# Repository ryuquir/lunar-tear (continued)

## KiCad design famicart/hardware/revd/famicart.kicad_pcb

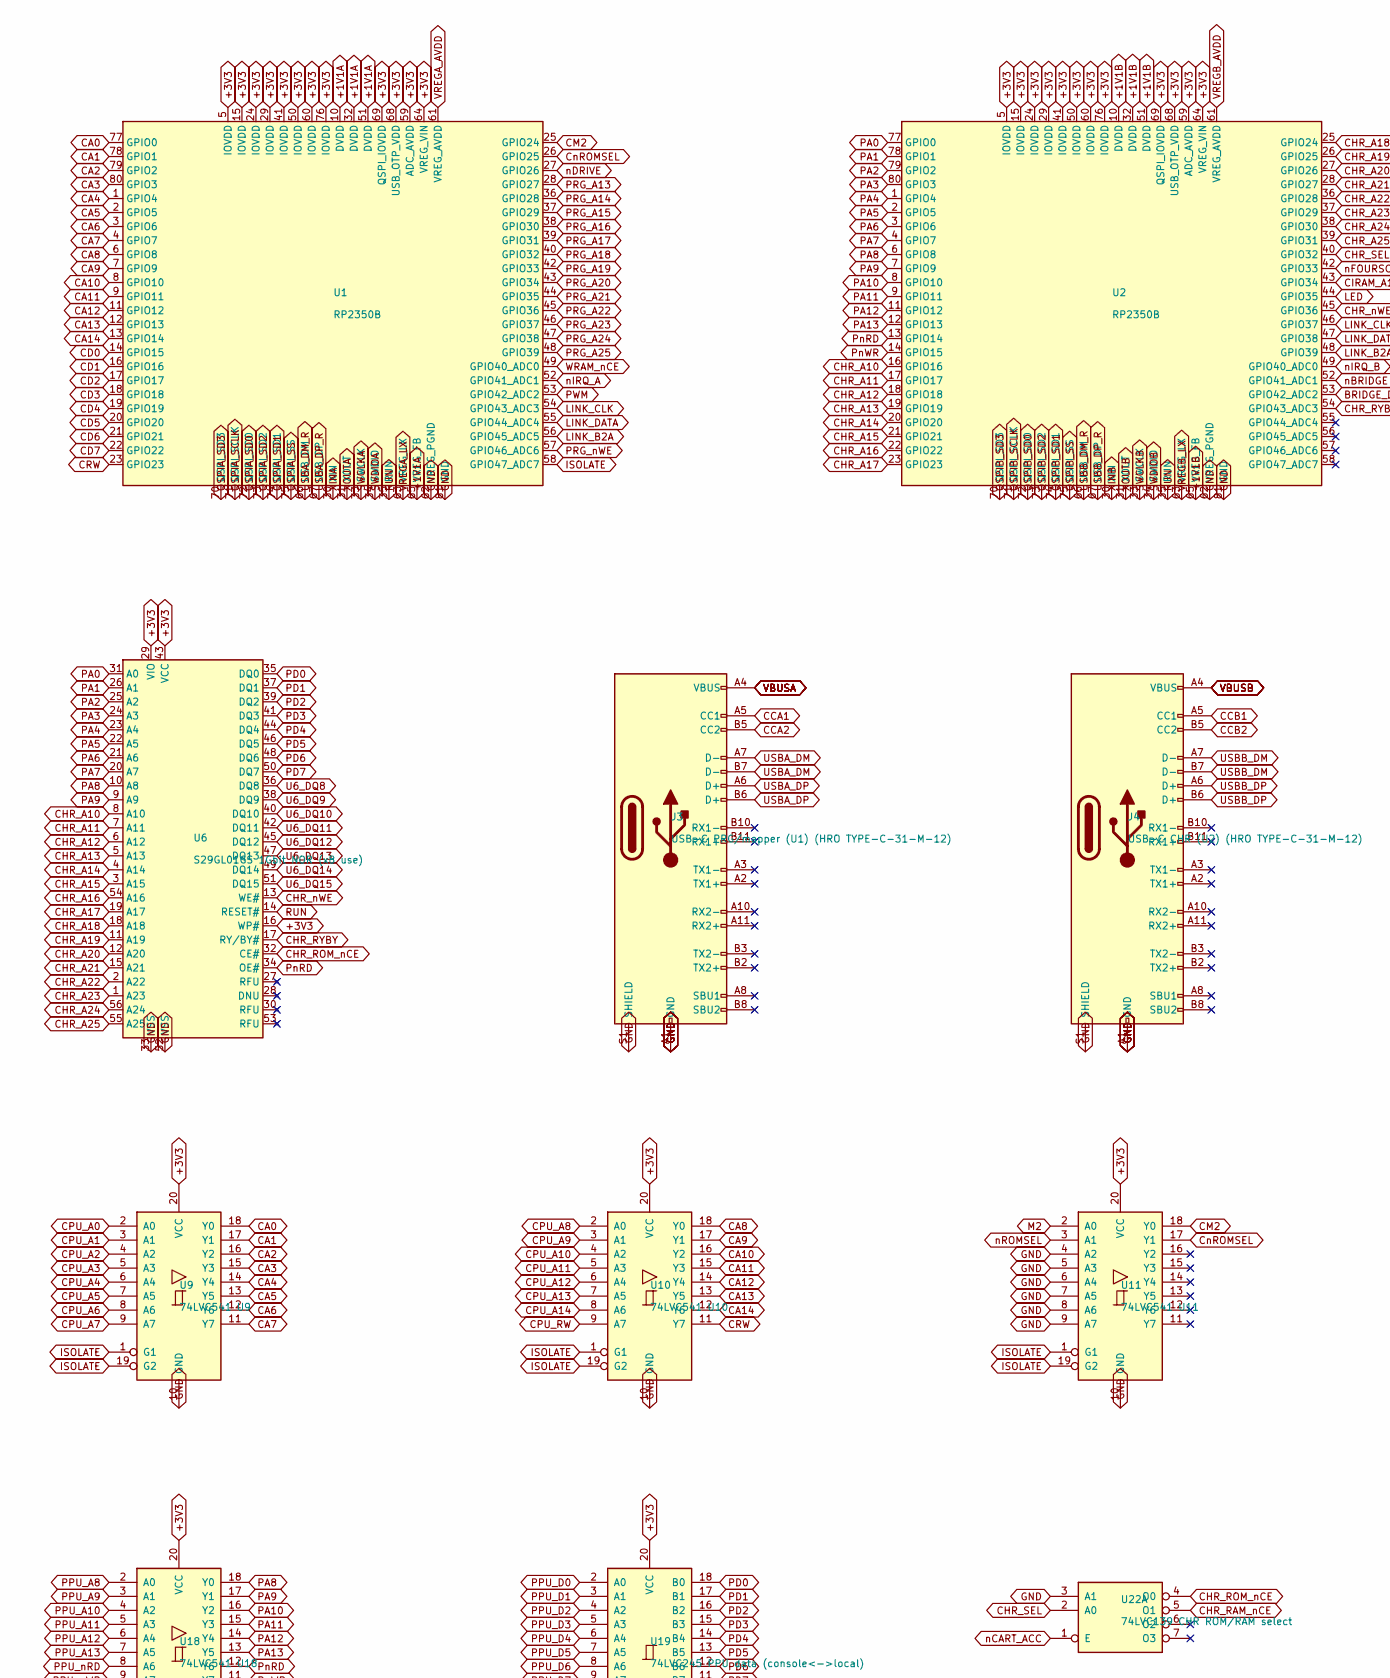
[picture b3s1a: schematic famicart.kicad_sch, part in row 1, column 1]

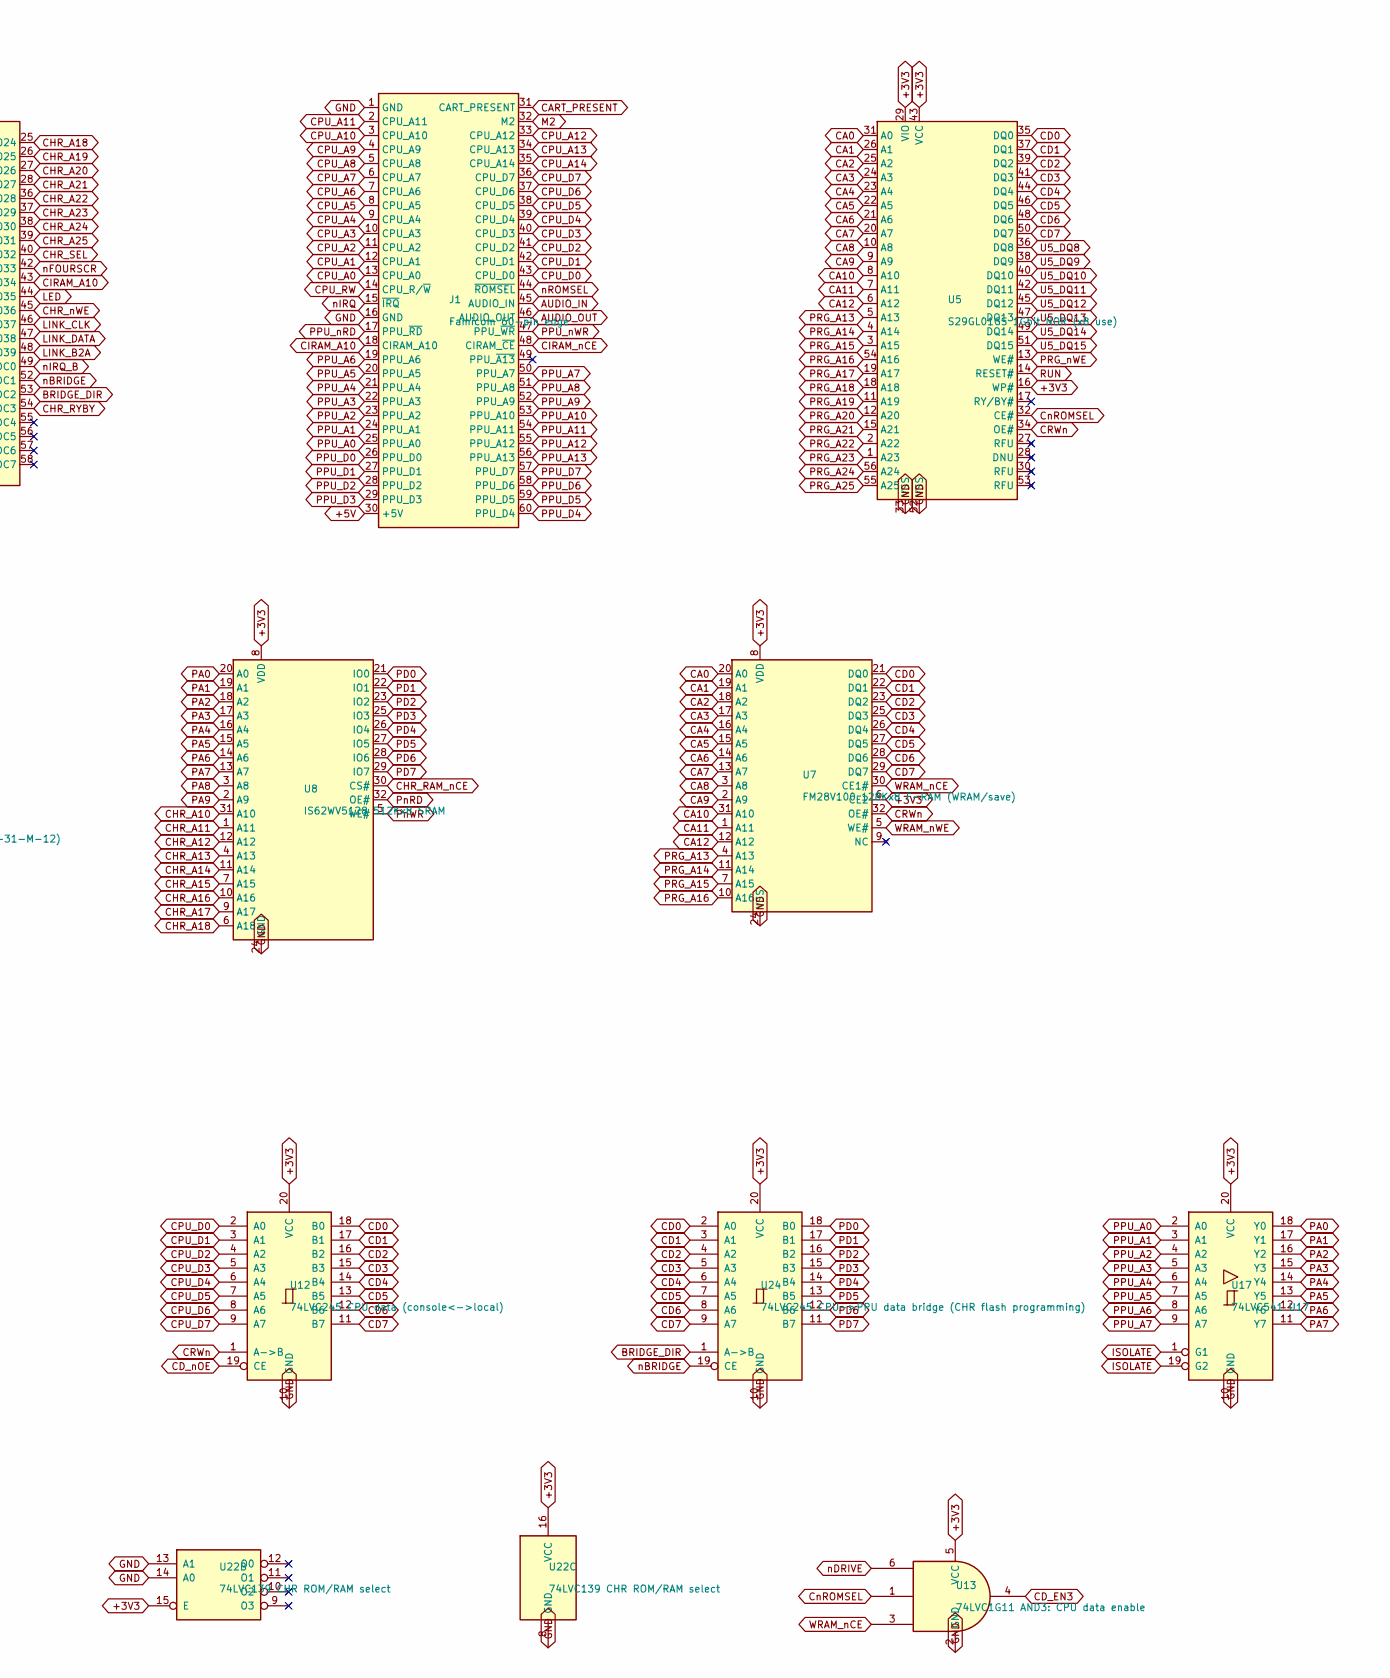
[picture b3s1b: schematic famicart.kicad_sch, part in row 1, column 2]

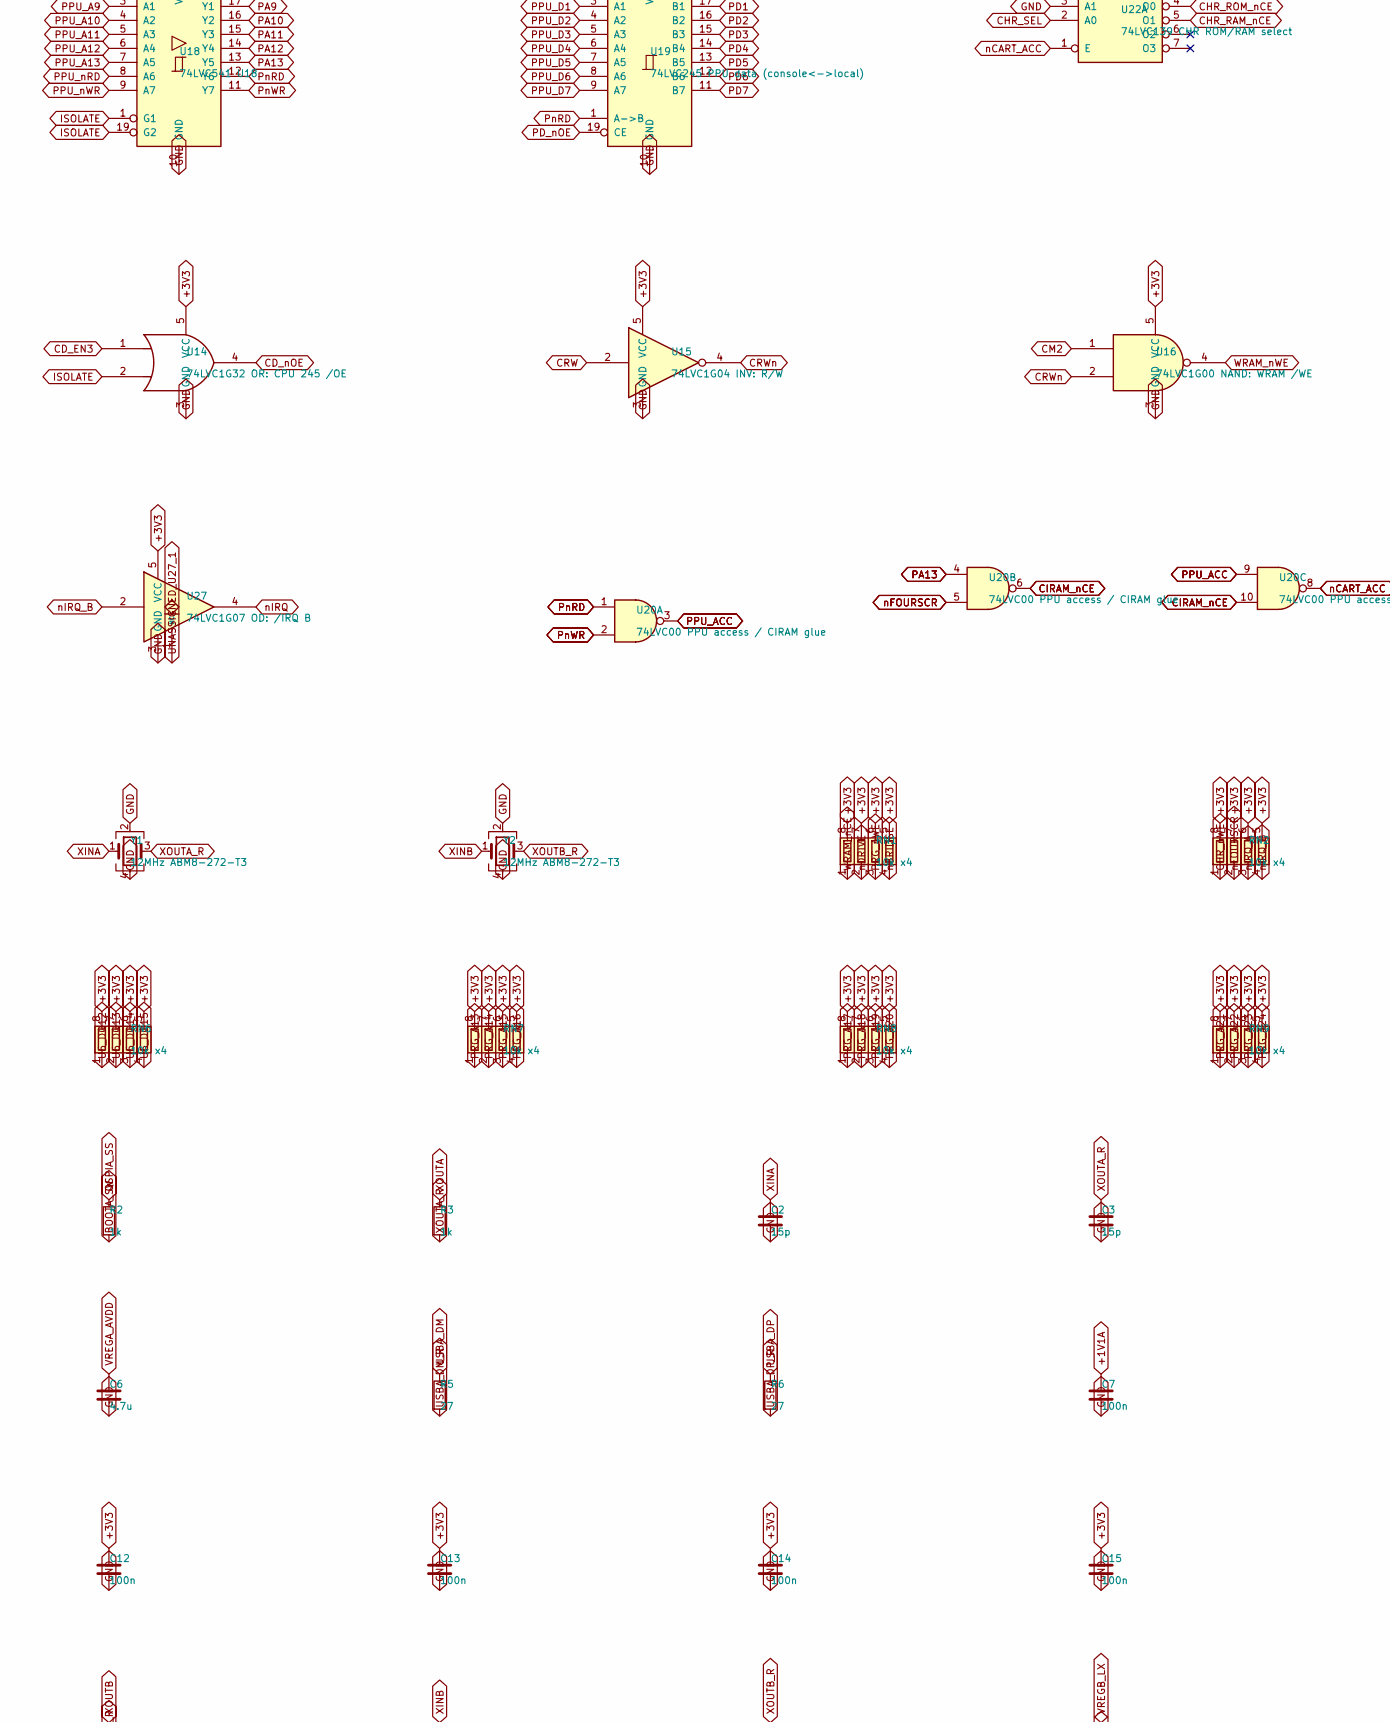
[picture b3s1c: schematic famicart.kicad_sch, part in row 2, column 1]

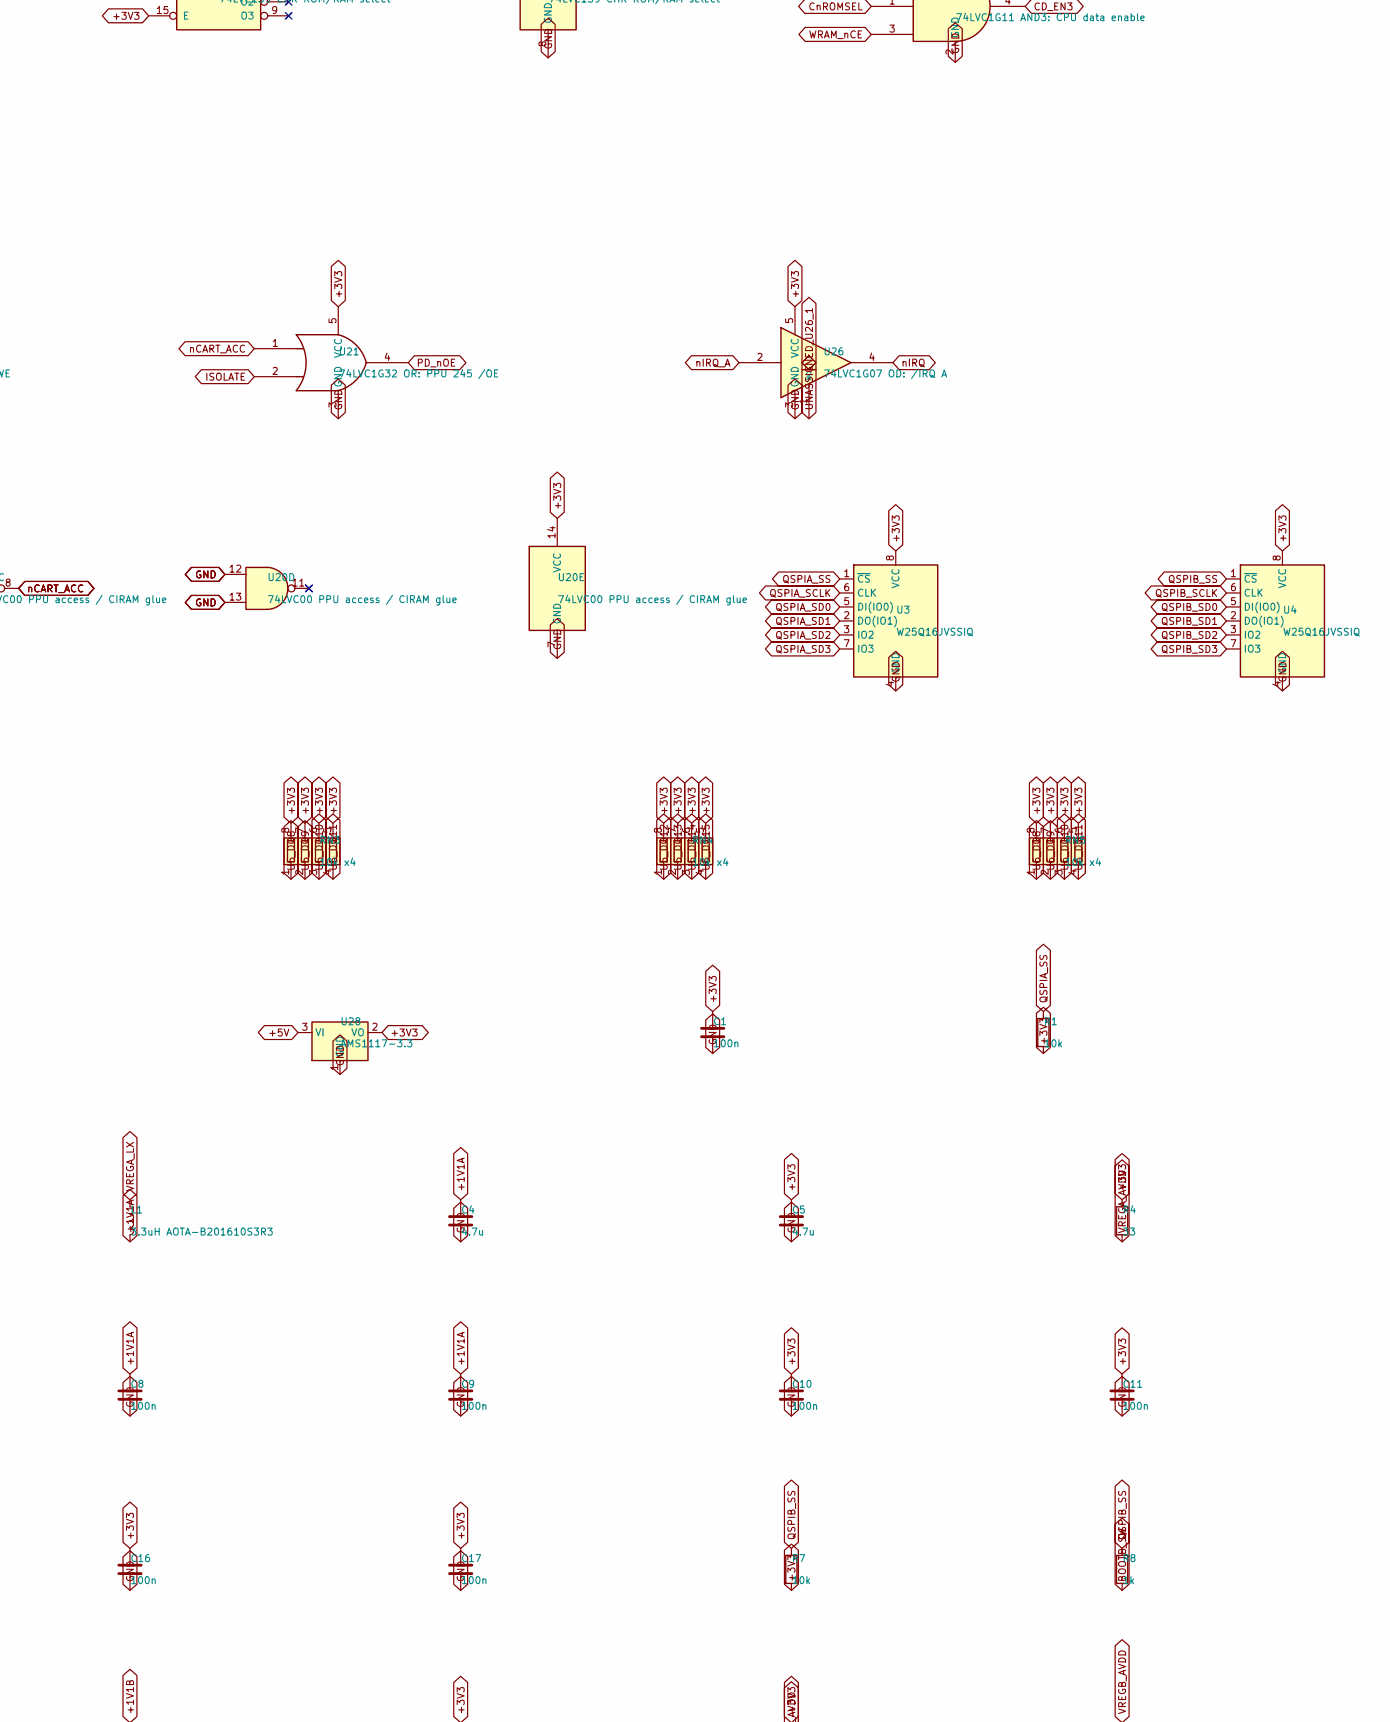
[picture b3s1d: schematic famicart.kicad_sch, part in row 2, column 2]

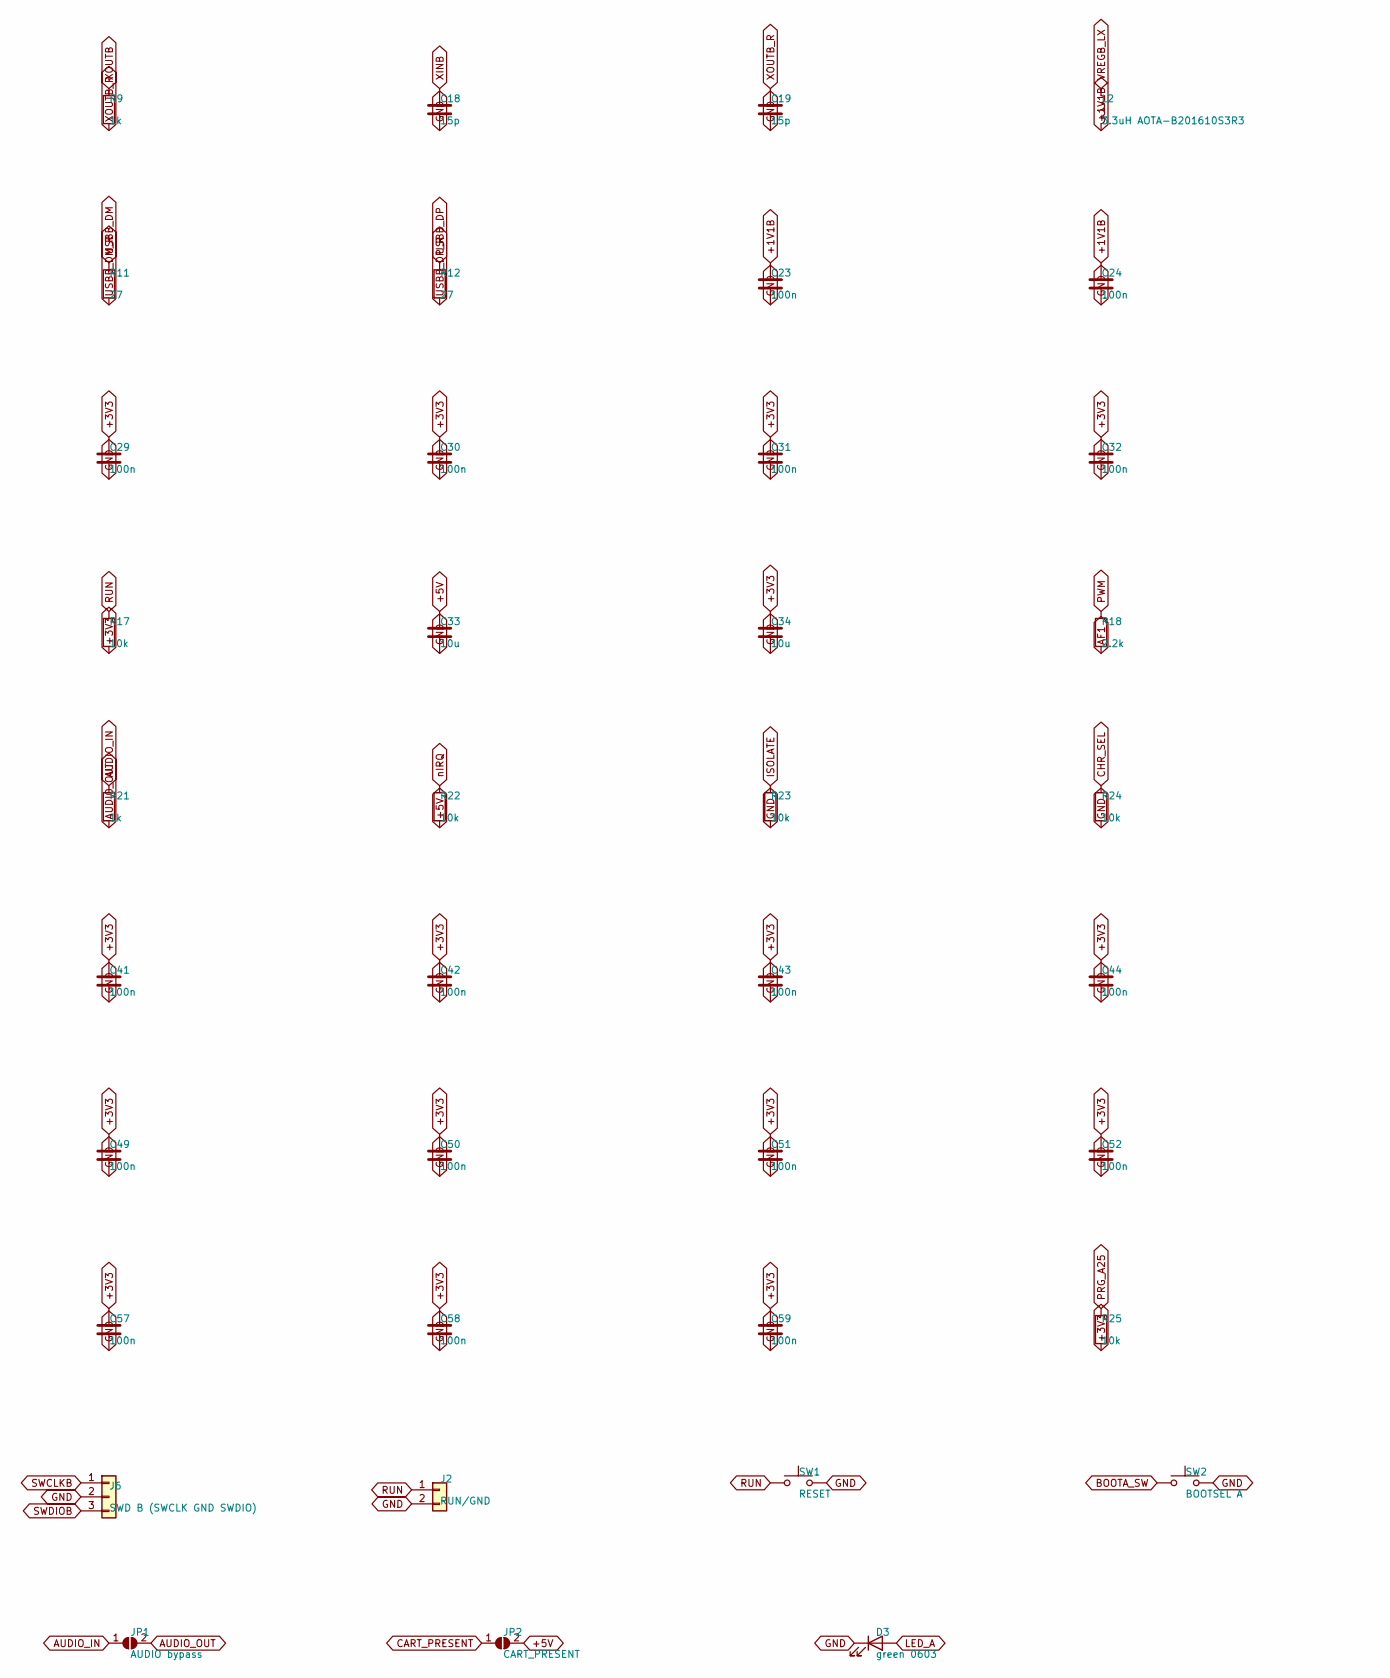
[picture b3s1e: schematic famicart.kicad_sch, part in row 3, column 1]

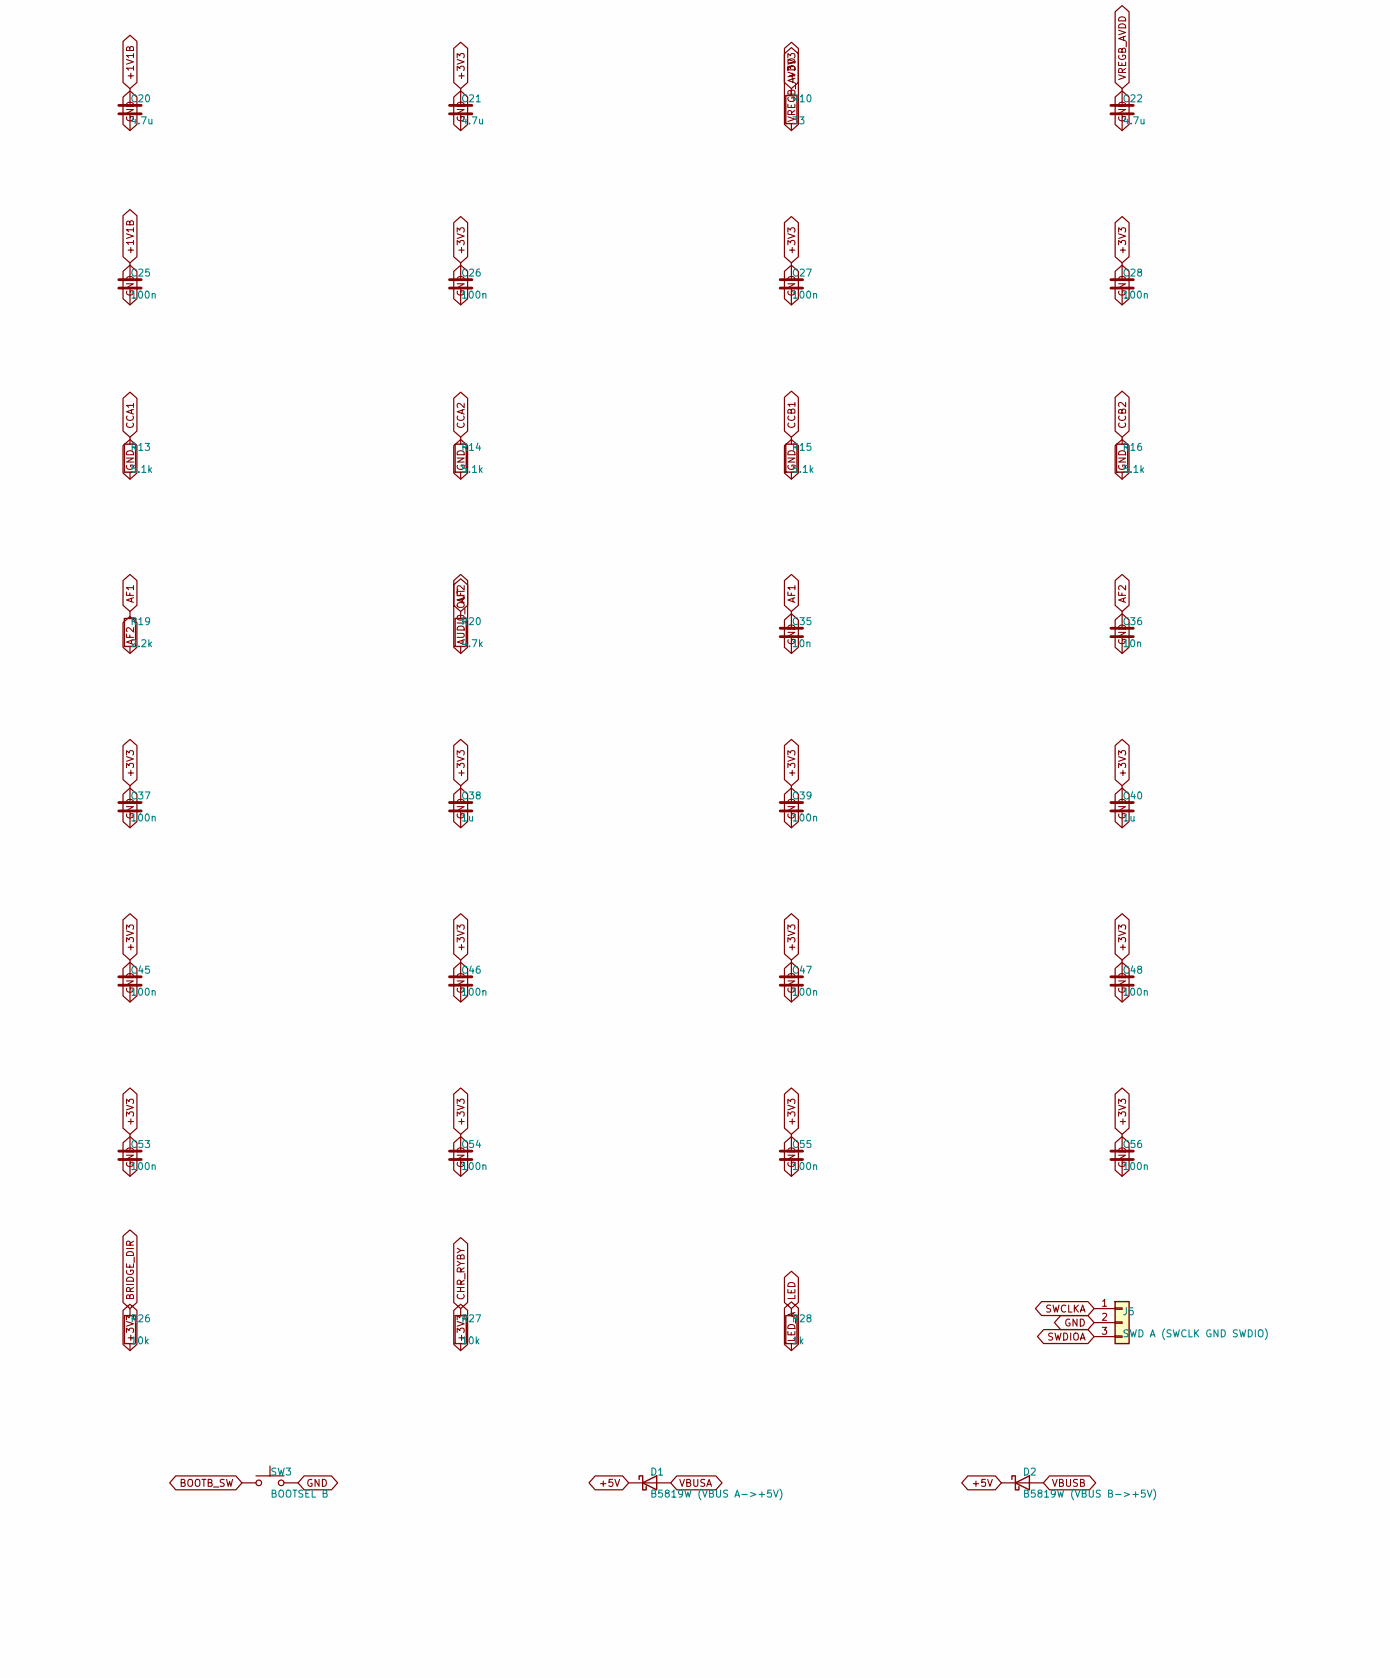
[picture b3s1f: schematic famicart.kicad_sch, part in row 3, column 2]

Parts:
C1, C17: 100n; C_0603_1608Metric
C2, C3, C18, C19: 15p; C_0402_1005Metric
C4, C5, C6, C20, C21, C22: 4.7u; C_0603_1608Metric
C7, C8, C9, C10, C11, C12, C13, C14, C15, C16, C23, C24, C25, C26, C27, C28, C29, C30, C31, C32, C37, C39, C41, C42, C43, C44, C45, C46, C47, C48, C49, C50, C51, C52, C53, C54, C55, C56, C57, C58, C59: 100n; C_0402_1005Metric
C33, C34: 10u; C_0805_2012Metric
C35, C36: 10n; C_0603_1608Metric
C38, C40: 1u; C_0603_1608Metric
D1: B5819W (VBUS A->+5V); D_SOD-123
D2: B5819W (VBUS B->+5V); D_SOD-123
D3: green 0603; LED_0603_1608Metric
J1: Famicom 60-pin edge; Famicom_CardEdge_60
J2: RUN/GND; PinHeader_1x02_P2.54mm_Vertical
J3: USB-C PRG/mapper (U1) (HRO TYPE-C-31-M-12); USB_C_Receptacle_HRO_TYPE-C-31-M-12
J4: USB-C CHR (U2) (HRO TYPE-C-31-M-12); USB_C_Receptacle_HRO_TYPE-C-31-M-12
J5: SWD A (SWCLK GND SWDIO); PinHeader_1x03_P2.54mm_Vertical
J6: SWD B (SWCLK GND SWDIO); PinHeader_1x03_P2.54mm_Vertical
JP1: AUDIO bypass; SolderJumper-2_P1.3mm_Open_RoundedPad1.0x1.5mm
JP2: CART_PRESENT; SolderJumper-2_P1.3mm_Open_RoundedPad1.0x1.5mm
L1, L2: 3.3uH AOTA-B201610S3R3; L_0806_2016Metric
R1, R7, R17, R22, R23, R24, R25, R26, R27: 10k; R_0603_1608Metric
R2, R8, R21, R28: 1k; R_0603_1608Metric
R3, R9: 1k; R_0402_1005Metric
R4, R10: 33; R_0402_1005Metric
R5, R6, R11, R12: 27; R_0603_1608Metric
R13, R14, R15, R16: 5.1k; R_0603_1608Metric
R18, R19: 2.2k; R_0603_1608Metric
R20: 4.7k; R_0603_1608Metric
RN1, RN2, RN3, RN4, RN5, RN6, RN7, RN8, RN9: 10k x4; R_Array_Convex_4x0603
SW1: RESET; SW_SPST_TL3342
SW2: BOOTSEL A; SW_SPST_TL3342
SW3: BOOTSEL B; SW_SPST_TL3342
U1, U2: RP2350B; QFN-80-1EP_10x10mm_P0.4mm_EP3.4x3.4mm
U3, U4: W25Q16JVSSIQ; SOIC-8_5.23x5.23mm_P1.27mm
U5, U6: S29GL01GS 1Gbit NOR (x8 use); TSOP-I-56_18.4x14mm_P0.5mm
U7: FM28V100 128Kx8 F-RAM (WRAM/save); TSOP-I-32_11.8x8mm_P0.5mm
U8: IS62WV5128 512Kx8 SRAM; TSOP-I-32_11.8x8mm_P0.5mm
U9: 74LVC541 U9; TSSOP-20_4.4x6.5mm_P0.65mm
U10: 74LVC541 U10; TSSOP-20_4.4x6.5mm_P0.65mm
U11: 74LVC541 U11; TSSOP-20_4.4x6.5mm_P0.65mm
U12: 74LVC245 CPU data (console<->local); TSSOP-20_4.4x6.5mm_P0.65mm
U13: 74LVC1G11 AND3: CPU data enable; SOT-23-6
U14: 74LVC1G32 OR: CPU 245 /OE; SOT-23-5
U15: 74LVC1G04 INV: R/W; SOT-23-5
U16: 74LVC1G00 NAND: WRAM /WE; SOT-23-5
U17: 74LVC541 U17; TSSOP-20_4.4x6.5mm_P0.65mm
U18: 74LVC541 U18; TSSOP-20_4.4x6.5mm_P0.65mm
U19: 74LVC245 PPU data (console<->local); TSSOP-20_4.4x6.5mm_P0.65mm
U20: 74LVC00 PPU access / CIRAM glue; TSSOP-14_4.4x5mm_P0.65mm
U21: 74LVC1G32 OR: PPU 245 /OE; SOT-23-5
U22: 74LVC139 CHR ROM/RAM select; TSSOP-16_4.4x5mm_P0.65mm
U24: 74LVC245 CPU->PPU data bridge (CHR flash programm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; TSSOP-20_4.4x6.5mm_P0.65mm
U26: 74LVC1G07 OD: /IRQ A; SOT-23-5
U27: 74LVC1G07 OD: /IRQ B; SOT-23-5
U28: AMS1117-3.3; SOT-223-3_TabPin2
Y1, Y2: 12MHz ABM8-272-T3; Crystal_SMD_3225-4Pin_3.2x2.5mm

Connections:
+1V1A: C4.1, C7.1, C8.1, C9.1, L1.2, U1.10 (DVDD), U1.32 (DVDD), U1.51 (DVDD), U1.65 (VREG_FB)
+1V1B: C20.1, C23.1, C24.1, C25.1, L2.2, U2.10 (DVDD), U2.32 (DVDD), U2.51 (DVDD), U2.65 (VREG_FB)
+3V3: C1.1, C5.1, C10.1, C11.1, C12.1, C13.1, C14.1, C15.1, C16.1, C17.1, C21.1, C26.1, C27.1, C28.1, C29.1, C30.1, C31.1, C32.1, C34.1, C37.1, C38.1, C39.1, C40.1, C41.1, C42.1, C43.1, C44.1, C45.1, C46.1, C47.1, C48.1, C49.1, C50.1, C51.1, C52.1, C53.1, C54.1, C55.1, C56.1, C57.1, C58.1, C59.1, R1.2, R4.1, R7.2, R10.1, R17.2, R25.2, R26.2, R27.2, RN1.5 (R4.2), RN1.6 (R3.2), RN1.7 (R2.2), RN1.8 (R1.2), RN2.5 (R4.2), RN2.6 (R3.2), RN2.7 (R2.2), RN2.8 (R1.2), RN3.5 (R4.2), RN3.6 (R3.2), RN3.7 (R2.2), RN3.8 (R1.2), RN4.5 (R4.2), RN4.6 (R3.2), RN4.7 (R2.2), RN4.8 (R1.2), RN5.5 (R4.2), RN5.6 (R3.2), RN5.7 (R2.2), RN5.8 (R1.2), RN6.5 (R4.2), RN6.6 (R3.2), RN6.7 (R2.2), RN6.8 (R1.2), RN7.5 (R4.2), RN7.6 (R3.2), RN7.7 (R2.2), RN7.8 (R1.2), RN8.5 (R4.2), RN8.6 (R3.2), RN8.7 (R2.2), RN8.8 (R1.2), RN9.5 (R4.2), RN9.6 (R3.2), RN9.7 (R2.2), RN9.8 (R1.2), U1.5 (IOVDD), U1.15 (IOVDD), U1.24 (IOVDD), U1.29 (IOVDD), U1.41 (IOVDD), U1.50 (IOVDD), U1.59 (ADC_AVDD), U1.60 (IOVDD), U1.64 (VREG_VIN), U1.68 (USB_OTP_VDD), U1.69 (QSPI_IOVDD), U1.76 (IOVDD), U2.5 (IOVDD), U2.15 (IOVDD), U2.24 (IOVDD), U2.29 (IOVDD), U2.41 (IOVDD), U2.50 (IOVDD), U2.59 (ADC_AVDD), U2.60 (IOVDD), U2.64 (VREG_VIN), U2.68 (USB_OTP_VDD), U2.69 (QSPI_IOVDD), U2.76 (IOVDD), U3.8 (VCC), U4.8 (VCC), U5.16 (WP#), U5.29 (VIO), U5.43 (VCC), U6.16 (WP#), U6.29 (VIO), U6.43 (VCC), U7.6 (CE2)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
+5V: C33.1, D1.1 (K), D2.1 (K), J1.30 (+5V), JP2.2 (B), R22.2, U28.3 (VI)
AF1: C35.1, R18.2, R19.1
AF2: C36.1, R19.2, R20.1
AUDIO_IN: J1.45 (AUDIO_IN), JP1.1 (A), R21.1
AUDIO_OUT: J1.46 (AUDIO_OUT), JP1.2 (B), R20.2, R21.2
BOOTA_SW: R2.2, SW2.1
BOOTB_SW: R8.2, SW3.1
BRIDGE_DIR: R26.1, U2.53 (GPIO42_ADC2), U24.1 (A->B)
CA0: U1.77 (GPIO0), U5.31 (A0), U7.20 (A0), U9.18 (Y0)
CA1: U1.78 (GPIO1), U5.26 (A1), U7.19 (A1), U9.17 (Y1)
CA2: U1.79 (GPIO2), U5.25 (A2), U7.18 (A2), U9.16 (Y2)
CA3: U1.80 (GPIO3), U5.24 (A3), U7.17 (A3), U9.15 (Y3)
CA4: U1.1 (GPIO4), U5.23 (A4), U7.16 (A4), U9.14 (Y4)
CA5: U1.2 (GPIO5), U5.22 (A5), U7.15 (A5), U9.13 (Y5)
CA6: U1.3 (GPIO6), U5.21 (A6), U7.14 (A6), U9.12 (Y6)
CA7: U1.4 (GPIO7), U5.20 (A7), U7.13 (A7), U9.11 (Y7)
CA8: U1.6 (GPIO8), U5.10 (A8), U7.3 (A8), U10.18 (Y0)
CA9: U1.7 (GPIO9), U5.9 (A9), U7.2 (A9), U10.17 (Y1)
CA10: U1.8 (GPIO10), U5.8 (A10), U7.31 (A10), U10.16 (Y2)
CA11: U1.9 (GPIO11), U5.7 (A11), U7.1 (A11), U10.15 (Y3)
CA12: U1.11 (GPIO12), U5.6 (A12), U7.12 (A12), U10.14 (Y4)
CA13: U1.12 (GPIO13), U10.13 (Y5)
CA14: U1.13 (GPIO14), U10.12 (Y6)
CART_PRESENT: J1.31 (CART_PRESENT), JP2.1 (A)
CCA1: J3.A5 (CC1), R13.1
CCA2: J3.B5 (CC2), R14.1
CCB1: J4.A5 (CC1), R15.1
CCB2: J4.B5 (CC2), R16.1
CD0: U1.14 (GPIO15), U5.35 (DQ0), U7.21 (DQ0), U12.18 (B0), U24.2 (A0)
CD1: U1.16 (GPIO16), U5.37 (DQ1), U7.22 (DQ1), U12.17 (B1), U24.3 (A1)
CD2: U1.17 (GPIO17), U5.39 (DQ2), U7.23 (DQ2), U12.16 (B2), U24.4 (A2)
CD3: U1.18 (GPIO18), U5.41 (DQ3), U7.25 (DQ3), U12.15 (B3), U24.5 (A3)
CD4: U1.19 (GPIO19), U5.44 (DQ4), U7.26 (DQ4), U12.14 (B4), U24.6 (A4)
CD5: U1.20 (GPIO20), U5.46 (DQ5), U7.27 (DQ5), U12.13 (B5), U24.7 (A5)
CD6: U1.21 (GPIO21), U5.48 (DQ6), U7.28 (DQ6), U12.12 (B6), U24.8 (A6)
CD7: U1.22 (GPIO22), U5.50 (DQ7), U7.29 (DQ7), U12.11 (B7), U24.9 (A7)
CD_EN3: U13.4, U14.1
CD_nOE: U12.19 (CE), U14.4
CHR_A10: U2.16 (GPIO16), U6.8 (A10), U8.31 (A10)
CHR_A11: U2.17 (GPIO17), U6.7 (A11), U8.1 (A11)
CHR_A12: U2.18 (GPIO18), U6.6 (A12), U8.12 (A12)
CHR_A13: U2.19 (GPIO19), U6.5 (A13), U8.4 (A13)
CHR_A14: U2.20 (GPIO20), U6.4 (A14), U8.11 (A14)
CHR_A15: U2.21 (GPIO21), U6.3 (A15), U8.7 (A15)
CHR_A16: U2.22 (GPIO22), U6.54 (A16), U8.10 (A16)
CHR_A17: U2.23 (GPIO23), U6.19 (A17), U8.9 (A17)
CHR_A18: U2.25 (GPIO24), U6.18 (A18), U8.6 (A18)
CHR_A19: U2.26 (GPIO25), U6.11 (A19)
CHR_A20: U2.27 (GPIO26), U6.12 (A20)
CHR_A21: U2.28 (GPIO27), U6.15 (A21)
CHR_A22: U2.36 (GPIO28), U6.2 (A22)
CHR_A23: U2.37 (GPIO29), U6.1 (A23)
CHR_A24: U2.38 (GPIO30), U6.56 (A24)
CHR_A25: U2.39 (GPIO31), U6.55 (A25)
CHR_RAM_nCE: U8.30 (CS#), U22.5 (O1)
CHR_ROM_nCE: U6.32 (CE#), U22.4 (O0)
CHR_RYBY: R27.1, U2.54 (GPIO43_ADC3), U6.17 (RY/BY#)
CHR_SEL: R24.1, U2.40 (GPIO32), U22.2 (A0)
CHR_nWE: RN2.1 (R1.1), U2.45 (GPIO36), U6.13 (WE#)
CIRAM_A10: J1.18 (CIRAM_A10), U2.43 (GPIO34)
CIRAM_nCE: J1.48 (CIRAM_~CE), U20.6, U20.10
CM2: U1.25 (GPIO24), U11.18 (Y0), U16.1
CPU_A0: J1.13 (CPU_A0), U9.2 (A0)
CPU_A1: J1.12 (CPU_A1), U9.3 (A1)
CPU_A2: J1.11 (CPU_A2), U9.4 (A2)
CPU_A3: J1.10 (CPU_A3), U9.5 (A3)
CPU_A4: J1.9 (CPU_A4), U9.6 (A4)
CPU_A5: J1.8 (CPU_A5), U9.7 (A5)
CPU_A6: J1.7 (CPU_A6), U9.8 (A6)
CPU_A7: J1.6 (CPU_A7), U9.9 (A7)
CPU_A8: J1.5 (CPU_A8), U10.2 (A0)
CPU_A9: J1.4 (CPU_A9), U10.3 (A1)
CPU_A10: J1.3 (CPU_A10), U10.4 (A2)
CPU_A11: J1.2 (CPU_A11), U10.5 (A3)
CPU_A12: J1.33 (CPU_A12), U10.6 (A4)
CPU_A13: J1.34 (CPU_A13), U10.7 (A5)
CPU_A14: J1.35 (CPU_A14), U10.8 (A6)
CPU_D0: J1.43 (CPU_D0), U12.2 (A0)
CPU_D1: J1.42 (CPU_D1), U12.3 (A1)
CPU_D2: J1.41 (CPU_D2), U12.4 (A2)
CPU_D3: J1.40 (CPU_D3), U12.5 (A3)
CPU_D4: J1.39 (CPU_D4), U12.6 (A4)
CPU_D5: J1.38 (CPU_D5), U12.7 (A5)
CPU_D6: J1.37 (CPU_D6), U12.8 (A6)
CPU_D7: J1.36 (CPU_D7), U12.9 (A7)
CPU_RW: J1.14 (CPU_R/~W), U10.9 (A7)
CRW: U1.23 (GPIO23), U10.11 (Y7), U15.2
CRWn: U5.34 (OE#), U7.32 (OE#), U12.1 (A->B), U15.4, U16.2
CnROMSEL: U1.26 (GPIO25), U5.32 (CE#), U11.17 (Y1), U13.1
GND: C1.2, C2.2, C3.2, C4.2, C5.2, C6.2, C7.2, C8.2, C9.2, C10.2, C11.2, C12.2, C13.2, C14.2, C15.2, C16.2, C17.2, C18.2, C19.2, C20.2, C21.2, C22.2, C23.2, C24.2, C25.2, C26.2, C27.2, C28.2, C29.2, C30.2, C31.2, C32.2, C33.2, C34.2, C35.2, C36.2, C37.2, C38.2, C39.2, C40.2, C41.2, C42.2, C43.2, C44.2, C45.2, C46.2, C47.2, C48.2, C49.2, C50.2, C51.2, C52.2, C53.2, C54.2, C55.2, C56.2, C57.2, C58.2, C59.2, D3.1 (K), J1.1 (GND), J1.16 (GND), J2.2, J3.A1 (GND), J3.A12 (GND), J3.B1 (GND), J3.B12 (GND), J3.S1 (SHIELD), J4.A1 (GND), J4.A12 (GND), J4.B1 (GND), J4.B12 (GND), J4.S1 (SHIELD), J5.2, J6.2, R13.2, R14.2, R15.2, R16.2, R23.2, R24.2, SW1.2, SW2.2, SW3.2, U1.62 (VREG_PGND), U1.81 (GND), U2.62 (VREG_PGND), U2.81 (GND), U3.4 (GND), U4.4 (GND), U5.33 (VSS), U5.52 (VSS), U6.33 (VSS), U6.52 (VSS), U7.24 (VSS), U8.24 (GND), U9.10 (GND), U10.10 (GND), U11.4 (A2), U11.5 (A3), U11.6 (A4), U11.7 (A5), U11.8 (A6), U11.9 (A7), U11.10 (GND), U12.10 (GND), U13.2 (GND), U14.3 (GND), U15.3 (GND), U16.3 (GND), U17.10 (GND), U18.10 (GND), U19.10 (GND), U20.7 (GND), U20.12, U20.13, U21.3 (GND), U22.3 (A1), U22.8 (GND)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
ISOLATE: R23.1, U1.58 (GPIO47_ADC7), U9.1 (G1), U9.19 (G2), U10.1 (G1), U10.19 (G2), U11.1 (G1), U11.19 (G2), U14.2, U17.1 (G1), U17.19 (G2), U18.1 (G1), U18.19 (G2), U21.2
LED: R28.1, U2.44 (GPIO35)
LED_A: D3.2 (A), R28.2
LINK_B2A: U1.56 (GPIO45_ADC5), U2.48 (GPIO39)
LINK_CLK: U1.54 (GPIO43_ADC3), U2.46 (GPIO37)
LINK_DATA: U1.55 (GPIO44_ADC4), U2.47 (GPIO38)
M2: J1.32 (M2), U11.2 (A0)
PA0: U2.77 (GPIO0), U6.31 (A0), U8.20 (A0), U17.18 (Y0)
PA1: U2.78 (GPIO1), U6.26 (A1), U8.19 (A1), U17.17 (Y1)
PA2: U2.79 (GPIO2), U6.25 (A2), U8.18 (A2), U17.16 (Y2)
PA3: U2.80 (GPIO3), U6.24 (A3), U8.17 (A3), U17.15 (Y3)
PA4: U2.1 (GPIO4), U6.23 (A4), U8.16 (A4), U17.14 (Y4)
PA5: U2.2 (GPIO5), U6.22 (A5), U8.15 (A5), U17.13 (Y5)
PA6: U2.3 (GPIO6), U6.21 (A6), U8.14 (A6), U17.12 (Y6)
PA7: U2.4 (GPIO7), U6.20 (A7), U8.13 (A7), U17.11 (Y7)
PA8: U2.6 (GPIO8), U6.10 (A8), U8.3 (A8), U18.18 (Y0)
PA9: U2.7 (GPIO9), U6.9 (A9), U8.2 (A9), U18.17 (Y1)
PA10: U2.8 (GPIO10), U18.16 (Y2)
PA11: U2.9 (GPIO11), U18.15 (Y3)
PA12: U2.11 (GPIO12), U18.14 (Y4)
PA13: U2.12 (GPIO13), U18.13 (Y5), U20.4
PD0: U6.35 (DQ0), U8.21 (IO0), U19.18 (B0), U24.18 (B0)
PD1: U6.37 (DQ1), U8.22 (IO1), U19.17 (B1), U24.17 (B1)
PD2: U6.39 (DQ2), U8.23 (IO2), U19.16 (B2), U24.16 (B2)
PD3: U6.41 (DQ3), U8.25 (IO3), U19.15 (B3), U24.15 (B3)
PD4: U6.44 (DQ4), U8.26 (IO4), U19.14 (B4), U24.14 (B4)
PD5: U6.46 (DQ5), U8.27 (IO5), U19.13 (B5), U24.13 (B5)
PD6: U6.48 (DQ6), U8.28 (IO6), U19.12 (B6), U24.12 (B6)
PD7: U6.50 (DQ7), U8.29 (IO7), U19.11 (B7), U24.11 (B7)
PD_nOE: U19.19 (CE), U21.4
PPU_A0: J1.25 (PPU_A0), U17.2 (A0)
PPU_A1: J1.24 (PPU_A1), U17.3 (A1)
PPU_A2: J1.23 (PPU_A2), U17.4 (A2)
PPU_A3: J1.22 (PPU_A3), U17.5 (A3)
PPU_A4: J1.21 (PPU_A4), U17.6 (A4)
PPU_A5: J1.20 (PPU_A5), U17.7 (A5)
PPU_A6: J1.19 (PPU_A6), U17.8 (A6)
PPU_A7: J1.50 (PPU_A7), U17.9 (A7)
PPU_A8: J1.51 (PPU_A8), U18.2 (A0)
PPU_A9: J1.52 (PPU_A9), U18.3 (A1)
PPU_A10: J1.53 (PPU_A10), U18.4 (A2)
PPU_A11: J1.54 (PPU_A11), U18.5 (A3)
PPU_A12: J1.55 (PPU_A12), U18.6 (A4)
PPU_A13: J1.56 (PPU_A13), U18.7 (A5)
PPU_ACC: U20.3, U20.9
PPU_D0: J1.26 (PPU_D0), U19.2 (A0)
PPU_D1: J1.27 (PPU_D1), U19.3 (A1)
PPU_D2: J1.28 (PPU_D2), U19.4 (A2)
PPU_D3: J1.29 (PPU_D3), U19.5 (A3)
PPU_D4: J1.60 (PPU_D4), U19.6 (A4)
PPU_D5: J1.59 (PPU_D5), U19.7 (A5)
PPU_D6: J1.58 (PPU_D6), U19.8 (A6)
PPU_D7: J1.57 (PPU_D7), U19.9 (A7)
PPU_nRD: J1.17 (PPU_~RD), U18.8 (A6)
PPU_nWR: J1.47 (PPU_~WR), U18.9 (A7)
PRG_A13: RN7.1 (R1.1), U1.28 (GPIO27), U5.5 (A13), U7.4 (A13)
PRG_A14: RN7.2 (R2.1), U1.36 (GPIO28), U5.4 (A14), U7.11 (A14)
PRG_A15: RN7.3 (R3.1), U1.37 (GPIO29), U5.3 (A15), U7.7 (A15)
PRG_A16: RN7.4 (R4.1), U1.38 (GPIO30), U5.54 (A16), U7.10 (A16)
PRG_A17: RN8.1 (R1.1), U1.39 (GPIO31), U5.19 (A17)
PRG_A18: RN8.2 (R2.1), U1.40 (GPIO32), U5.18 (A18)
PRG_A19: RN8.3 (R3.1), U1.42 (GPIO33), U5.11 (A19)
PRG_A20: RN8.4 (R4.1), U1.43 (GPIO34), U5.12 (A20)
PRG_A21: RN9.1 (R1.1), U1.44 (GPIO35), U5.15 (A21)
PRG_A22: RN9.2 (R2.1), U1.45 (GPIO36), U5.2 (A22)
PRG_A23: RN9.3 (R3.1), U1.46 (GPIO37), U5.1 (A23)
PRG_A24: RN9.4 (R4.1), U1.47 (GPIO38), U5.56 (A24)
PRG_A25: R25.1, U1.48 (GPIO39), U5.55 (A25)
PRG_nWE: RN1.3 (R3.1), U1.57 (GPIO46_ADC6), U5.13 (WE#)
PWM: R18.1, U1.53 (GPIO42_ADC2)
PnRD: U2.13 (GPIO14), U6.34 (OE#), U8.32 (OE#), U18.12 (Y6), U19.1 (A->B), U20.1
PnWR: U2.14 (GPIO15), U8.5 (WE#), U18.11 (Y7), U20.2
QSPIA_SCLK: U1.71 (QSPI_SCLK), U3.6 (CLK)
QSPIA_SD0: U1.72 (QSPI_SD0), U3.5 (DI(IO0))
QSPIA_SD1: U1.74 (QSPI_SD1), U3.2 (DO(IO1))
QSPIA_SD2: U1.73 (QSPI_SD2), U3.3 (IO2)
QSPIA_SD3: U1.70 (QSPI_SD3), U3.7 (IO3)
QSPIA_SS: R1.1, R2.1, U1.75 (QSPI_SS), U3.1 (~CS)
QSPIB_SCLK: U2.71 (QSPI_SCLK), U4.6 (CLK)
QSPIB_SD0: U2.72 (QSPI_SD0), U4.5 (DI(IO0))
QSPIB_SD1: U2.74 (QSPI_SD1), U4.2 (DO(IO1))
QSPIB_SD2: U2.73 (QSPI_SD2), U4.3 (IO2)
QSPIB_SD3: U2.70 (QSPI_SD3), U4.7 (IO3)
QSPIB_SS: R7.1, R8.1, U2.75 (QSPI_SS), U4.1 (~CS)
RUN: J2.1, R17.1, SW1.1, U1.35 (RUN), U2.35 (RUN), U5.14 (RESET#), U6.14 (RESET#)
SWCLKA: J5.1, U1.33 (SWCLK)
SWCLKB: J6.1, U2.33 (SWCLK)
SWDIOA: J5.3, U1.34 (SWDIO)
SWDIOB: J6.3, U2.34 (SWDIO)
U5_DQ8: RN3.1 (R1.1), U5.36 (DQ8)
U5_DQ9: RN3.2 (R2.1), U5.38 (DQ9)
U5_DQ10: RN3.3 (R3.1), U5.40 (DQ10)
U5_DQ11: RN3.4 (R4.1), U5.42 (DQ11)
U5_DQ12: RN4.1 (R1.1), U5.45 (DQ12)
U5_DQ13: RN4.2 (R2.1), U5.47 (DQ13)
U5_DQ14: RN4.3 (R3.1), U5.49 (DQ14)
U5_DQ15: RN4.4 (R4.1), U5.51 (DQ15)
U6_DQ8: RN5.1 (R1.1), U6.36 (DQ8)
U6_DQ9: RN5.2 (R2.1), U6.38 (DQ9)
U6_DQ10: RN5.3 (R3.1), U6.40 (DQ10)
U6_DQ11: RN5.4 (R4.1), U6.42 (DQ11)
U6_DQ12: RN6.1 (R1.1), U6.45 (DQ12)
U6_DQ13: RN6.2 (R2.1), U6.47 (DQ13)
U6_DQ14: RN6.3 (R3.1), U6.49 (DQ14)
U6_DQ15: RN6.4 (R4.1), U6.51 (DQ15)
USBA_DM: J3.A7 (D-), J3.B7 (D-), R5.1
USBA_DM_R: R5.2, U1.66 (USB_DM)
USBA_DP: J3.A6 (D+), J3.B6 (D+), R6.1
USBA_DP_R: R6.2, U1.67 (USB_DP)
USBB_DM: J4.A7 (D-), J4.B7 (D-), R11.1
USBB_DM_R: R11.2, U2.66 (USB_DM)
USBB_DP: J4.A6 (D+), J4.B6 (D+), R12.1
USBB_DP_R: R12.2, U2.67 (USB_DP)
VBUSA: D1.2 (A), J3.A4 (VBUS), J3.A9 (VBUS), J3.B4 (VBUS), J3.B9 (VBUS)
VBUSB: D2.2 (A), J4.A4 (VBUS), J4.A9 (VBUS), J4.B4 (VBUS), J4.B9 (VBUS)
VREGA_AVDD: C6.1, R4.2, U1.61 (VREG_AVDD)
VREGA_LX: L1.1, U1.63 (VREG_LX)
VREGB_AVDD: C22.1, R10.2, U2.61 (VREG_AVDD)
VREGB_LX: L2.1, U2.63 (VREG_LX)
WRAM_nCE: RN1.1 (R1.1), U1.49 (GPIO40_ADC0), U7.30 (CE1#), U13.3
WRAM_nWE: U7.5 (WE#), U16.4
XINA: C2.1, U1.30 (XIN), Y1.1
XINB: C18.1, U2.30 (XIN), Y2.1
XOUTA: R3.1, U1.31 (XOUT)
XOUTA_R: C3.1, R3.2, Y1.3
XOUTB: R9.1, U2.31 (XOUT)
XOUTB_R: C19.1, R9.2, Y2.3
nBRIDGE: RN1.4 (R4.1), U2.52 (GPIO41_ADC1), U24.19 (CE)
nCART_ACC: U20.8, U21.1, U22.1 (E)
nDRIVE: RN1.2 (R2.1), U1.27 (GPIO26), U13.6
nFOURSCR: RN2.2 (R2.1), U2.42 (GPIO33), U20.5
nIRQ: J1.15 (~IRQ), R22.1, U26.4, U27.4
nIRQ_A: RN2.3 (R3.1), U1.52 (GPIO41_ADC1), U26.2
nIRQ_B: RN2.4 (R4.1), U2.49 (GPIO40_ADC0), U27.2
nROMSEL: J1.44 (~ROMSEL), U11.3 (A1)
